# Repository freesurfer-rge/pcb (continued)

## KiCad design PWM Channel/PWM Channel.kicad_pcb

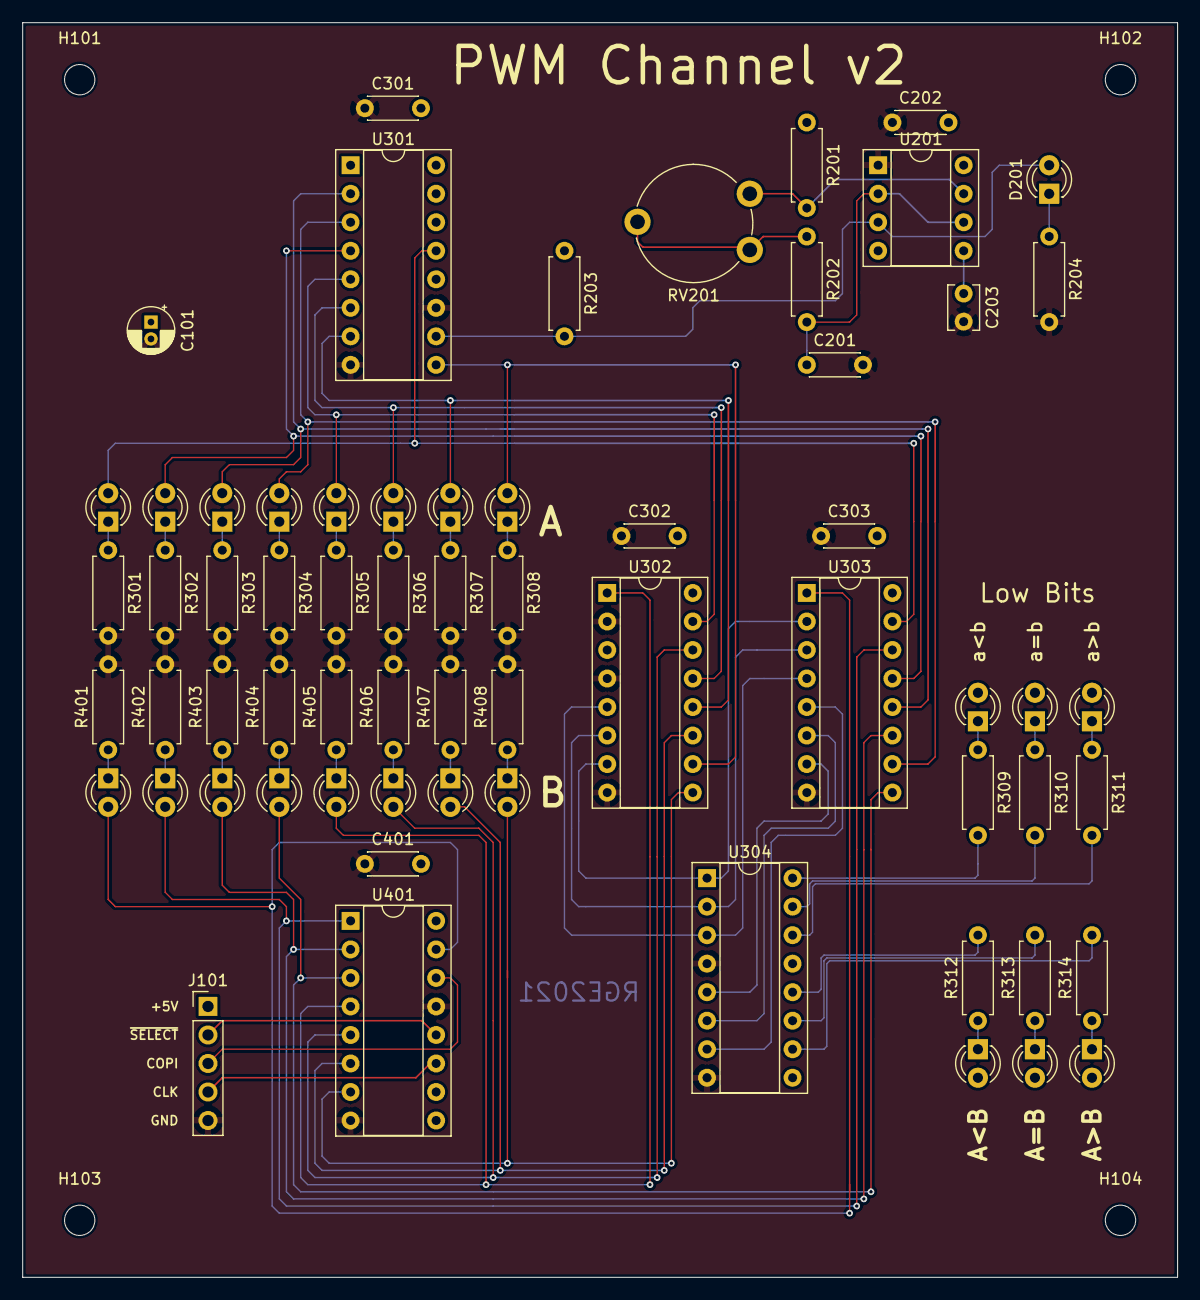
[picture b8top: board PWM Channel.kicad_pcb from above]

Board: 2 copper layers, 102.9 x 111.8 mm, 69 parts (0 on the bottom side), 61 nets.

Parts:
C101: CP; CP_Radial_D4.0mm_P1.50mm
C201, C202, C301, C302, C303, C401: 0.1uF; C_Disc_D4.3mm_W1.9mm_P5.00mm
C203: 0.01uF; C_Disc_D3.8mm_W2.6mm_P2.50mm
D201, D301, D302, D303, D304, D305, D306, D307, D308, D309, D310, D311, D312, D313, D314, D401, D402, D403, D404, D405, D406, D407, D408: LED; LED_D3.0mm
H101, H102, H103, H104: MountingHole; MountingHole_2.7mm_M2.5
J101: Conn_01x05_Male; PinHeader_1x05_P2.54mm_Vertical
R201, R202: 33; R_Axial_DIN0207_L6.3mm_D2.5mm_P7.62mm_Horizontal
R203, R309, R310, R311, R312, R313, R314: 1k; R_Axial_DIN0207_L6.3mm_D2.5mm_P7.62mm_Horizontal
R204, R301, R302, R303, R304, R305, R306, R307, R308, R401, R402, R403, R404, R405, R406, R407, R408: 4k7; R_Axial_DIN0207_L6.3mm_D2.5mm_P7.62mm_Horizontal
RV201: R_POT; Potentiometer_Piher_PT-10-V10_Vertical
U201: NE555P; DIP-8_W7.62mm_Socket
U301: 4040; DIP-16_W7.62mm_Socket
U302, U303: 7485; DIP-16_W7.62mm_Socket
U304: ULN2003A; DIP-16_W7.62mm_Socket
U401: 74HCT595; DIP-16_W7.62mm_Socket

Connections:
+5V: C101.1, C202.2, C301.2, C302.2, C303.2, C401.2, D309.2, D310.2, D311.2, D312.2, D313.2, D314.2, J101.1, R201.1, R203.1, U201.4, U201.8, U301.16, U302.3, U302.16, U303.16, U304.9, U401.10, U401.16
/Driver Clock/DIVIDER: R201.2, RV201.1, U201.7
/Driver Clock/TRTHR: C201.1, R202.2, U201.2, U201.6
/PWM/A00: D308.2, U301.9, U302.10
/PWM/A01: D307.2, U301.7, U302.12
/PWM/A02: D306.2, U301.6, U302.13
/PWM/A03: D305.2, U301.5, U302.15
/PWM/A04: D304.2, U301.3, U303.10
/PWM/A05: D303.2, U301.2, U303.12
/PWM/A06: D302.2, U301.4, U303.13
/PWM/A07: D301.2, U301.13, U303.15
/PWM/B00: D408.2, U302.9, U401.7
/PWM/B01: D407.2, U302.11, U401.6
/PWM/B02: D406.2, U302.14, U401.5
/PWM/B03: D405.2, U302.1, U401.4
/PWM/B04: D404.2, U303.9, U401.3
/PWM/B05: D403.2, U303.11, U401.2
/PWM/B06: D402.2, U303.14, U401.1
/PWM/B07: D401.2, U303.1, U401.15
/PWM/DRIVER: D201.2, R203.2, U201.3, U301.10
/SPI Input/CLK: J101.4, U401.11
/SPI Input/COPI: J101.3, U401.14
/SPI Input/~SELECT: J101.2, U401.12
GND: C101.2, C201.2, C202.1, C203.2, C301.1, C302.1, C303.1, C401.1, J101.5, R204.2, R301.2, R302.2, R303.2, R304.2, R305.2, R306.2, R307.2, R308.2, R401.2, R402.2, R403.2, R404.2, R405.2, R406.2, R407.2, R408.2, U201.1, U301.8, U301.11, U302.2, U302.4, U302.8, U303.8, U304.4, U304.8, U401.8, U401.13
unnamed: C203.1, U201.5
unnamed: D201.1, R204.1
unnamed: D301.1, R301.1
unnamed: D302.1, R302.1
unnamed: D303.1, R303.1
unnamed: D304.1, R304.1
unnamed: D305.1, R305.1
unnamed: D306.1, R306.1
unnamed: D307.1, R307.1
unnamed: D308.1, R308.1
unnamed: D309.1, R309.1
unnamed: D310.1, R310.1
unnamed: D311.1, R311.1
unnamed: D312.1, R312.1
unnamed: D313.1, R313.1
unnamed: D314.1, R314.1
unnamed: D401.1, R401.1
unnamed: D402.1, R402.1
unnamed: D403.1, R403.1
unnamed: D404.1, R404.1
unnamed: D405.1, R405.1
unnamed: D406.1, R406.1
unnamed: D407.1, R407.1
unnamed: D408.1, R408.1
unnamed: R202.1, RV201.2, RV201.3
unnamed: R309.2, U304.16
unnamed: R310.2, U304.15
unnamed: R311.2, U304.14
unnamed: R312.2, U304.12
unnamed: R313.2, U304.11
unnamed: R314.2, U304.10
unnamed: U302.5, U303.4, U304.3
unnamed: U302.6, U303.3, U304.2
unnamed: U302.7, U303.2, U304.1
unnamed: U303.5, U304.7
unnamed: U303.6, U304.6
unnamed: U303.7, U304.5
